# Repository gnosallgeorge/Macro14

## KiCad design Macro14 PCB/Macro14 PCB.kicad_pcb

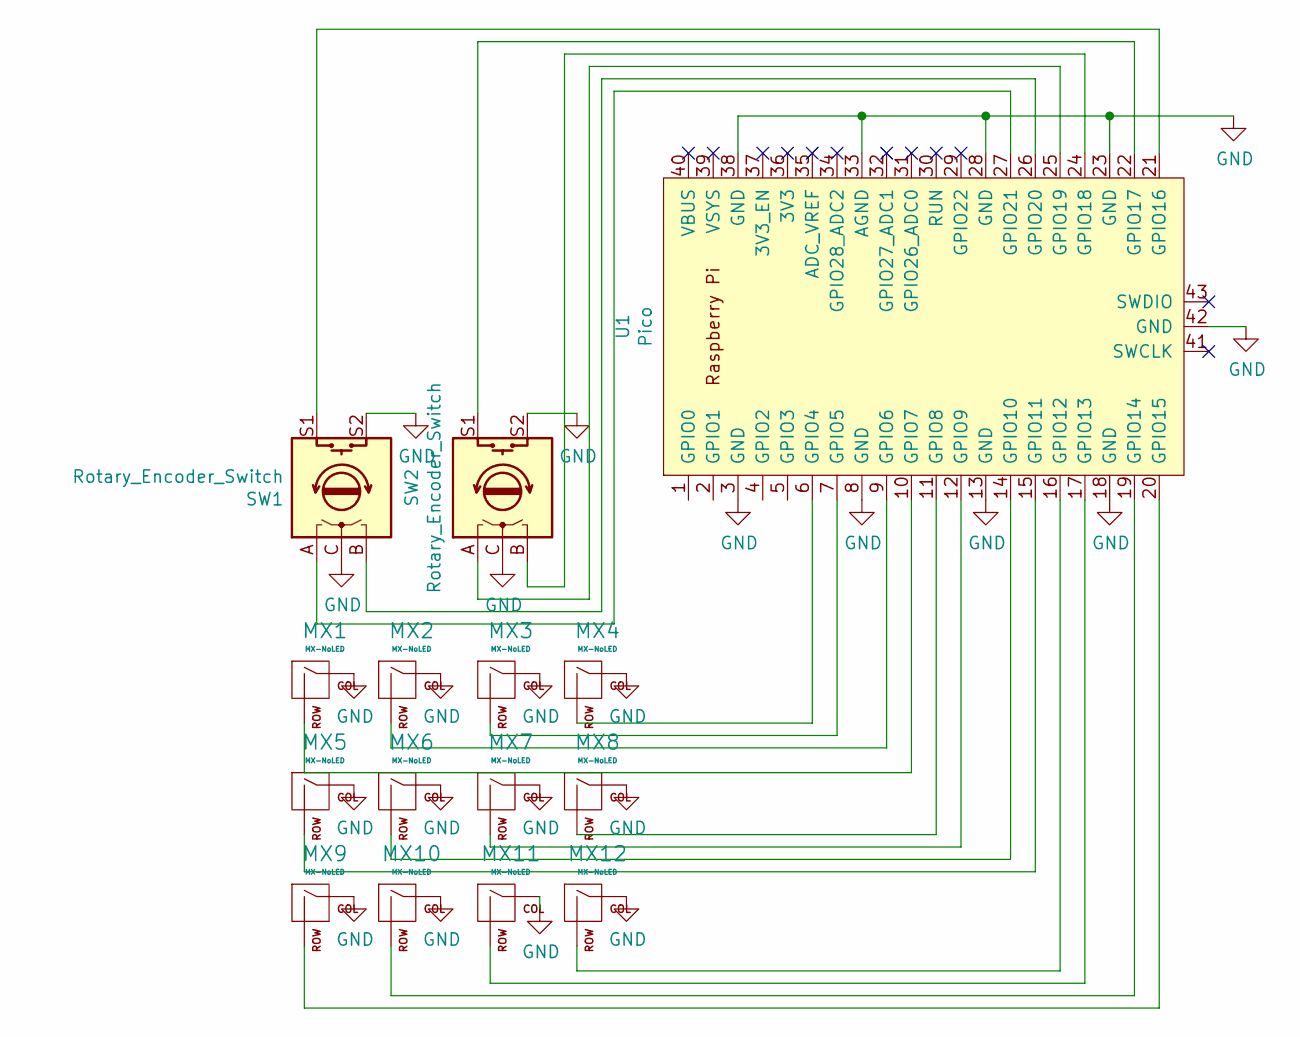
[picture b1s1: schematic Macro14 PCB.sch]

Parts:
MX1, MX2, MX3, MX4, MX5, MX6, MX7, MX8, MX9, MX10, MX11, MX12: MX-NoLED; MXOnly-1U-NoLED
SW1, SW2: Rotary_Encoder_Switch; RotaryEncoder_Alps_EC11E-Switch_Vertical_H20mm_CircularMoun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
U1: Pico; RPi_Pico_SMD_TH

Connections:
GND: MX1.1 (COL), MX2.1 (COL), MX3.1 (COL), MX4.1 (COL), MX5.1 (COL), MX6.1 (COL), MX7.1 (COL), MX8.1 (COL), MX9.1 (COL), MX10.1 (COL), MX11.1 (COL), MX12.1 (COL), SW1.C, SW1.S2, SW2.C, SW2.S2, U1.3 (GND), U1.8 (GND), U1.13 (GND), U1.18 (GND), U1.23 (GND), U1.28 (GND), U1.33 (AGND), U1.38 (GND), U1.42 (GND)
unnamed: MX1.2 (ROW), U1.10 (GPIO7)
unnamed: MX2.2 (ROW), U1.9 (GPIO6)
unnamed: MX3.2 (ROW), U1.7 (GPIO5)
unnamed: MX4.2 (ROW), U1.6 (GPIO4)
unnamed: MX5.2 (ROW), U1.15 (GPIO11)
unnamed: MX6.2 (ROW), U1.14 (GPIO10)
unnamed: MX7.2 (ROW), U1.12 (GPIO9)
unnamed: MX8.2 (ROW), U1.11 (GPIO8)
unnamed: MX9.2 (ROW), U1.20 (GPIO15)
unnamed: MX10.2 (ROW), U1.19 (GPIO14)
unnamed: MX11.2 (ROW), U1.17 (GPIO13)
unnamed: MX12.2 (ROW), U1.16 (GPIO12)
unnamed: SW1.A, U1.27 (GPIO21)
unnamed: SW1.B, U1.26 (GPIO20)
unnamed: SW1.S1, U1.21 (GPIO16)
unnamed: SW2.A, U1.25 (GPIO19)
unnamed: SW2.B, U1.24 (GPIO18)
unnamed: SW2.S1, U1.22 (GPIO17)

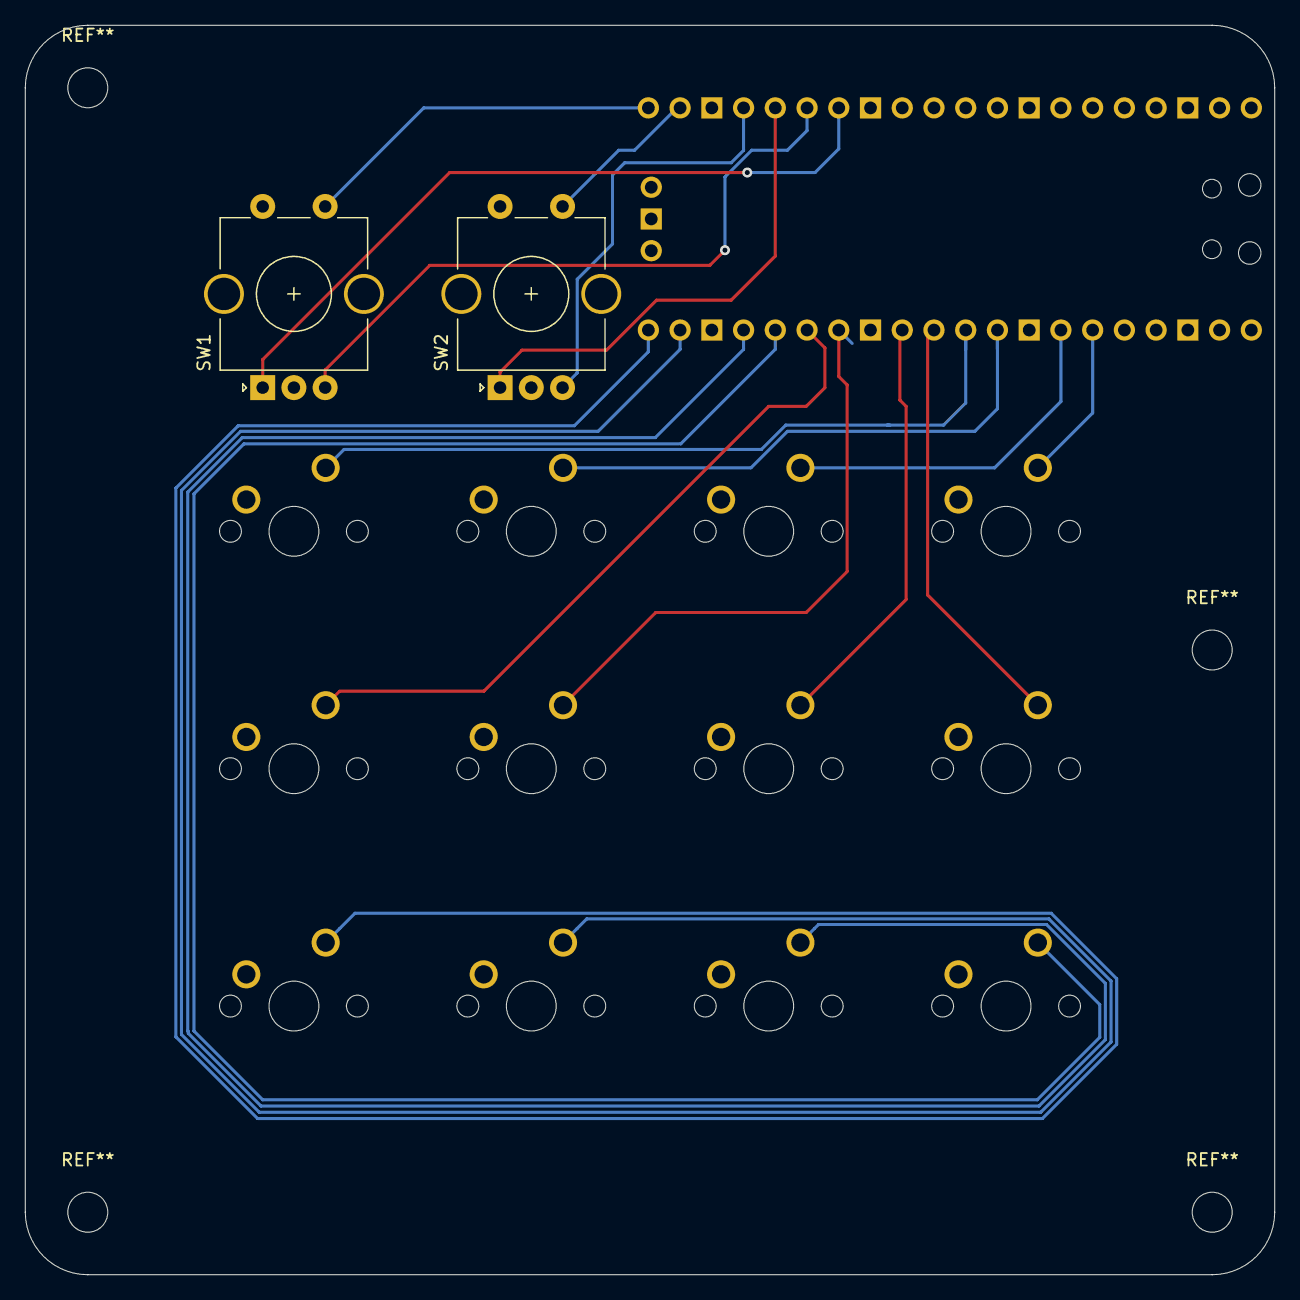
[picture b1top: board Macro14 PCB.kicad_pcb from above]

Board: 2 copper layers, 100.0 x 100.0 mm, 15 parts (1 on the bottom side), 19 nets.

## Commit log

2023-01-22 Blank PCB file
2023-01-22 added necessary PCB submodules
2023-01-22 Create sym-lib-table
2023-01-22 added ec11 and rp pico schematics
2023-01-26 Appended functioning Pico schematic and footprint
2023-01-26 basic schematic created
2023-02-01 Finished Schematic
2023-02-01 started pcb
2023-02-02 PCB completed and schematic updated
